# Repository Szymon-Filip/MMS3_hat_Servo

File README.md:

# Hat 4-kanałowy sterownik serw

## Sekcja 1: Dokumentacja Hat'a

### Krótki opis projektu
Hat to 4-kanałowy sterownik serw, bazujący na  generatorze PWM **PCA9685PW** (komunikacja I2C). Zasialnie serw jest z XT60

### Zgodność ze standardem ChainBus

* ✅ Używa złącza ChainBus, nie zmienia jego miejsca ani pinoutu.
* ✅ Używa wyłącznie interfejsów I2C, SPI lub UART i nie inicjuje samodzielnie nowych transmisji (Nie jest master'em I2C albo SPI).
* ✅ Spełnia wymagania mechaniczne standardu (wymiary PCB, rozstaw otworów).
* ✅ Pobiera maksymalny prąd zgodny z ilością na jednego hat'a
* ✅ Obsługuje napięcie wejściowe BRD_VIN do wartości 48V.

### Komunikacja i adresowanie

#### Adresacja I2C
Komunikacja z PCA9685PW odbywa się za pomocą magistrali I2C. Wszystkie linie adresowe układu PCA9685PW (A0, A1, A2, A3, A4, A5) są podłączone do napięcia 5V.

| Układ (IC)    | Funkcja                          | Adres I2C (7-bit) |
| :------------ | :------------------------------- | :---------------: |
| **PCA9685PW** | 16-kanałowy generator PWM 12-bit | `1111111b` (0x7F) |

---

### Przypisanie kanałów generatora PCA9685

Układ PCA9685 steruje bezpośrednio czterema wyjściami serw oraz dwoma debug diodami LED:

| Wyjście PCA9685 | Powiązany element | Typ złącza  | Opis                              |
| :-------------: | :---------------- | :---------- | :-------------------------------- |
|    **LED0**     | Servo 1           | **J10**     | Kanał sterujący serwomechanizmu 1 |
|    **LED1**     | Servo 2           | **J9**      | Kanał sterujący serwomechanizmu 2 |
|    **LED2**     | Servo 3           | **J8**      | Kanał sterujący serwomechanizmu 3 |
|    **LED3**     | Servo 4           | **J7**      | Kanał sterujący serwomechanizmu 4 |
|    **LED14**    | Debug LED         | *Na płycie* | Dioda LED do debugowania          |
|    **LED15**    | Debug LED         | *Na płycie* | Dioda LED do debugowania          |

---

### Pinout złączy serwomechanizmów (J7 – J10)

Każde złącze wyjściowe (J7, J8, J9, J10) posiada 3 piny w następującym układzie:

| Pin   | Nazwa sygnału | Poziom napięcia    | Opis                                       |
| :---- | :------------ | :----------------- | :----------------------------------------- |
| **1** | `GND`         | 0 V                | Wspólna masa układu                        |
| **2** | `SERVO` (PWM) | 5 V                | Sygnał sterujący PWM z układu PCA9685      |
| **3** | `VCC`         | `BRD_VIN` (z XT60) | Napięcie zasilające silnik serwomechanizmu |

> **⚠️ UWAGA DOTYCZĄCA BEZPIECZEŃSTWA (PINOUT):**
> Układ wyprowadzeń złączy na tym module to **[1: GND, 2: Sygnał, 3: VCC]**. Jest on odmienny od klasycznego modelarskiego standardu wtyczek serwomechanizmów (gdzie pin zasilania VCC zazwyczaj znajduje się w środku wtyku).
>
> Przed podłączeniem serwomechanizmu należy bezwzględnie zweryfikować kolejność przewodów w wiązce serwa. Błędne podłączenie może skutkować uszkodzeniem serwa lub obwodów zasilania modułu.

---

### Szczegółowy opis techniczny

#### Zasilanie serwomechanizmów (`VCC`)
Prąd zasilania serwomechanizmów nie obciąża wewnętrznych linii zasilających magistrali ChainBus. Napięcie doprowadzane jest bezpośrednio ze złącza wysokoprądowego **XT60** na pin 3 każdego złącza serwa. Zasilanie z XT-60 od razu idzie na szyne VIN ChainBus'a. Jeśli potrzebujesz zasilić serwa innym napięciem niż takim samym jak VIN ChainBus'a to odlutuj D1 (tą diode po lewej stronie do której idzie taka duża ścieżka)

#### Sterowanie sygnałem PWM
PWM jest na 5V, ale szyna I2C na 3V3 więc wszystko śmiga jak powinno

---

### Gotowe arkusze hierarchiczne
W projekcie wydzielono i zastosowano następujące arkusze hierarchiczne:
* **Servo_controller** – Schemat generatora PWM PCA9685 z konwerterem I2C 3v3 <-> 5V i zworkami do wybierania adresu I2C

---

## Sekcja 2: Specyfikacja standardu ChainBus

### Architektura i łączenie modułów
Standard ChainBus umożliwia modułowe łączenie hatów. Na jednym MMS3 można zamontować pionowo **do 8 hat'ów**. Połączenie realizowane jest poprzez wpięcie złącza męskiego kolejnego hat'a w złącze żeńskie poprzedniego.

### Komunikacja i sterowanie
Magistrala ChainBus jest w pełni cyfrowa. Płyta główna nie steruje bezpośrednio sygnałami ogólnego przeznaczenia (GPIO) na poszczególnych hat'ach. Wszelkie operacje (np. generowanie sygnałów PWM, obsługa diod) muszą być realizowane przez dedykowane układy scalone komunikujące się przez interfejsy systemowe.

Wybór aktywnego modułu realizowany jest przez układ przełącznika magistrali (bus switch) na płycie głównej. Dzięki temu linie I2C, SPI i UART są niezależne dla każdego hat'a (brak konfliktów adresów I2C między różnymi hatami).
* **Identyfikacja:** Każdy moduł powinien posiadać pamięć EEPROM na magistrali I2C w celu identyfikacji płyty przez system - układ M24C64-W skonfigurowany na adres `1010000` przy liniach adresowych A0, A1, A2 zwartych do masy.

### Zasilanie
Złącze ChainBus dostarcza następujące linie zasilania:

| Magistrala zasilania | Napięcie znamionowe | Maksymalny prąd (łączny dla 8 hatów) | Szacowany prąd na jeden hat |
| :------------------- | :-----------------: | :----------------------------------: | :-------------------------: |
| **5V**               |        5.0 V        |                1.0 A                 |           125 mA            |
| **12V stby**         |       12.0 V        |                0.5 A                 |            65 mA            |
| **BRD_VIN**          |   12.0 V – 48.0 V   |                1.5 A                 |           185 mA            |

*   W przypadku zapotrzebowania na wyższą moc (jak w przypadku tego modułu sterowania serwami), stosuje się dodatkowe złącze zasilania XT60 (obciążalność do ok. 60 A).

---

## Sekcja 3: Licencja, linki i tagi

### Licencjonowanie projektu

*   **PCB:** [CERN-OHL-W](https://ohwr.org/project/cernohl/wikis/Documents/CERN-OHL-version-2) - Umożliwia modyfikacje i sprzedaż pod warunkiem zachowania informacji o oryginalnym autorze. Zmiany muszą być open source.
*   **Software:** [MIT License](https://opensource.org/licenses/MIT) - Umożliwia modyfikacje i sprzedaż komercyjną pod warunkiem zachowania informacji o autorze (zmiany nie muszą być udostępniane jako open source).

### Tagi projektu
#chainbus #MMS3 #ModuCard

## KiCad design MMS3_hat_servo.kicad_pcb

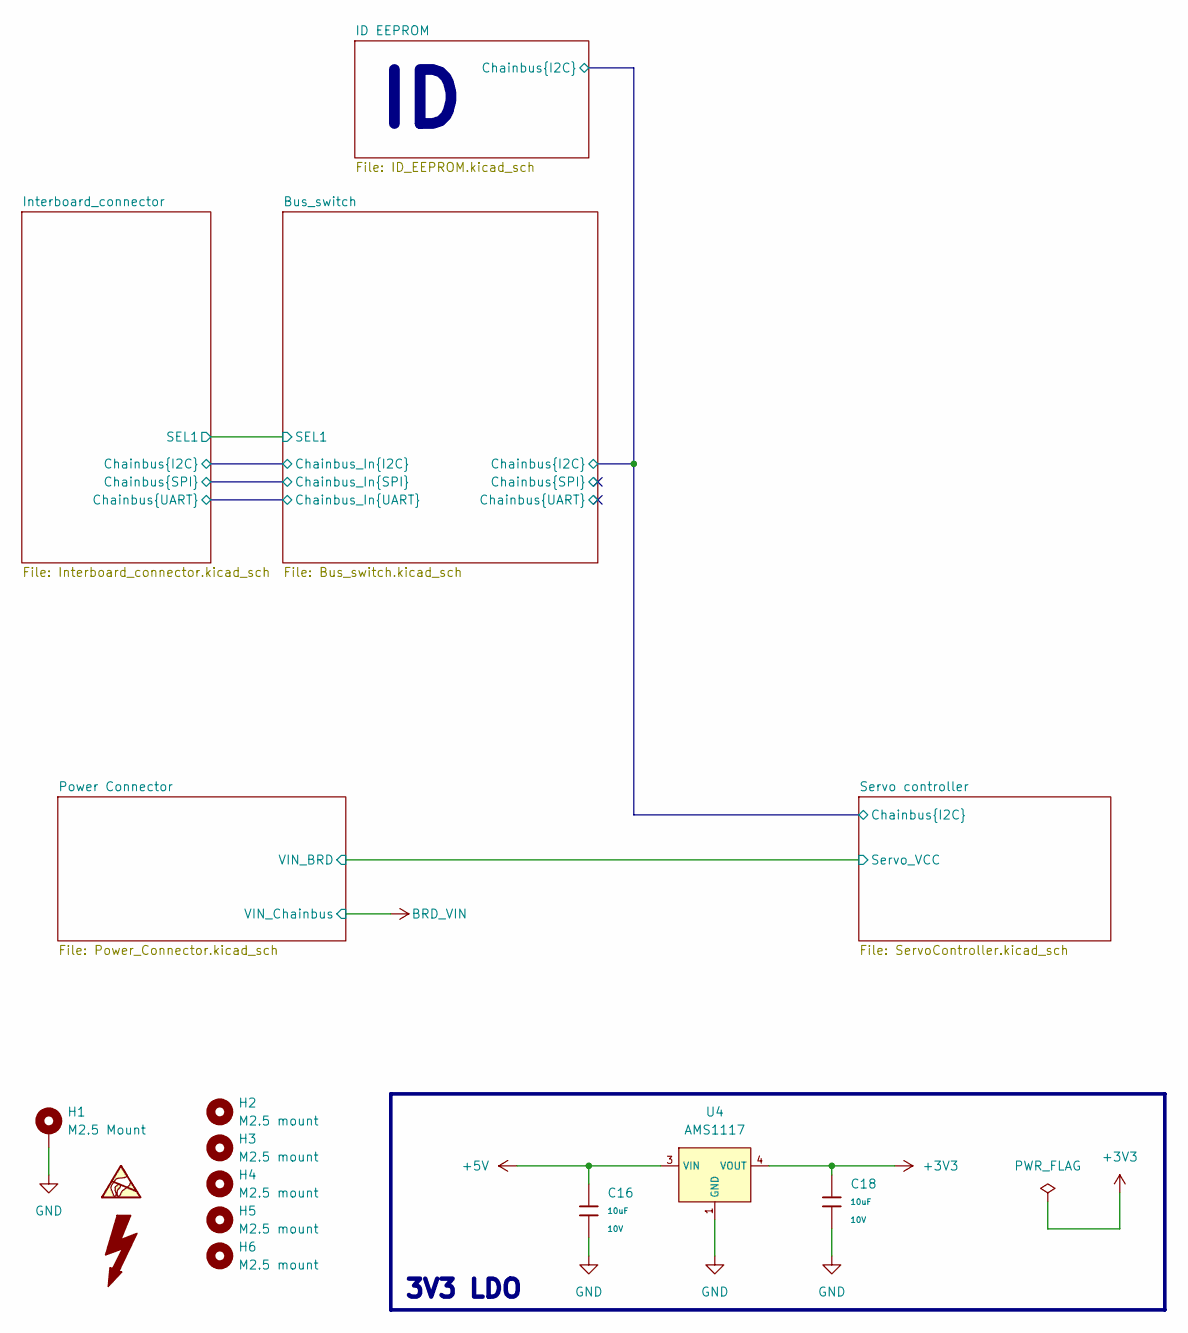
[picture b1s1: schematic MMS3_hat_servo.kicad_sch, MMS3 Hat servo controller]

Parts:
C16, C18: 10uF; C_0603; Voltage Rated 10V; Tolerance ±10%; Part CL10A106KP8NNNC; LCSC C19702
H1: M2.5 Mount; MountingHole_2.7mm_M2.5_DIN965_Pad_TopOnly
H2, H3, H4, H5, H6: M2.5 mount; MountingHole_2.7mm_M2.5
U4: AMS1117; SOT-223-3_L6.5-W3.4-P2.30-LS7.0-BR; Output Voltage 3.3V; Dropout Voltage 1.3V@(800mA); Part AMS1117-3.3; LCSC C6186

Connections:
+3V3: C18.1, U4.2 (VOUT), U4.4 (VOUT); also elsewhere on the board
+5V: C16.1, U4.3 (VIN); also elsewhere on the board
GND: C16.2, C18.2, H1.1 (1_1), U4.1 (GND); also elsewhere on the board

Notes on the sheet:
3V3 LDO

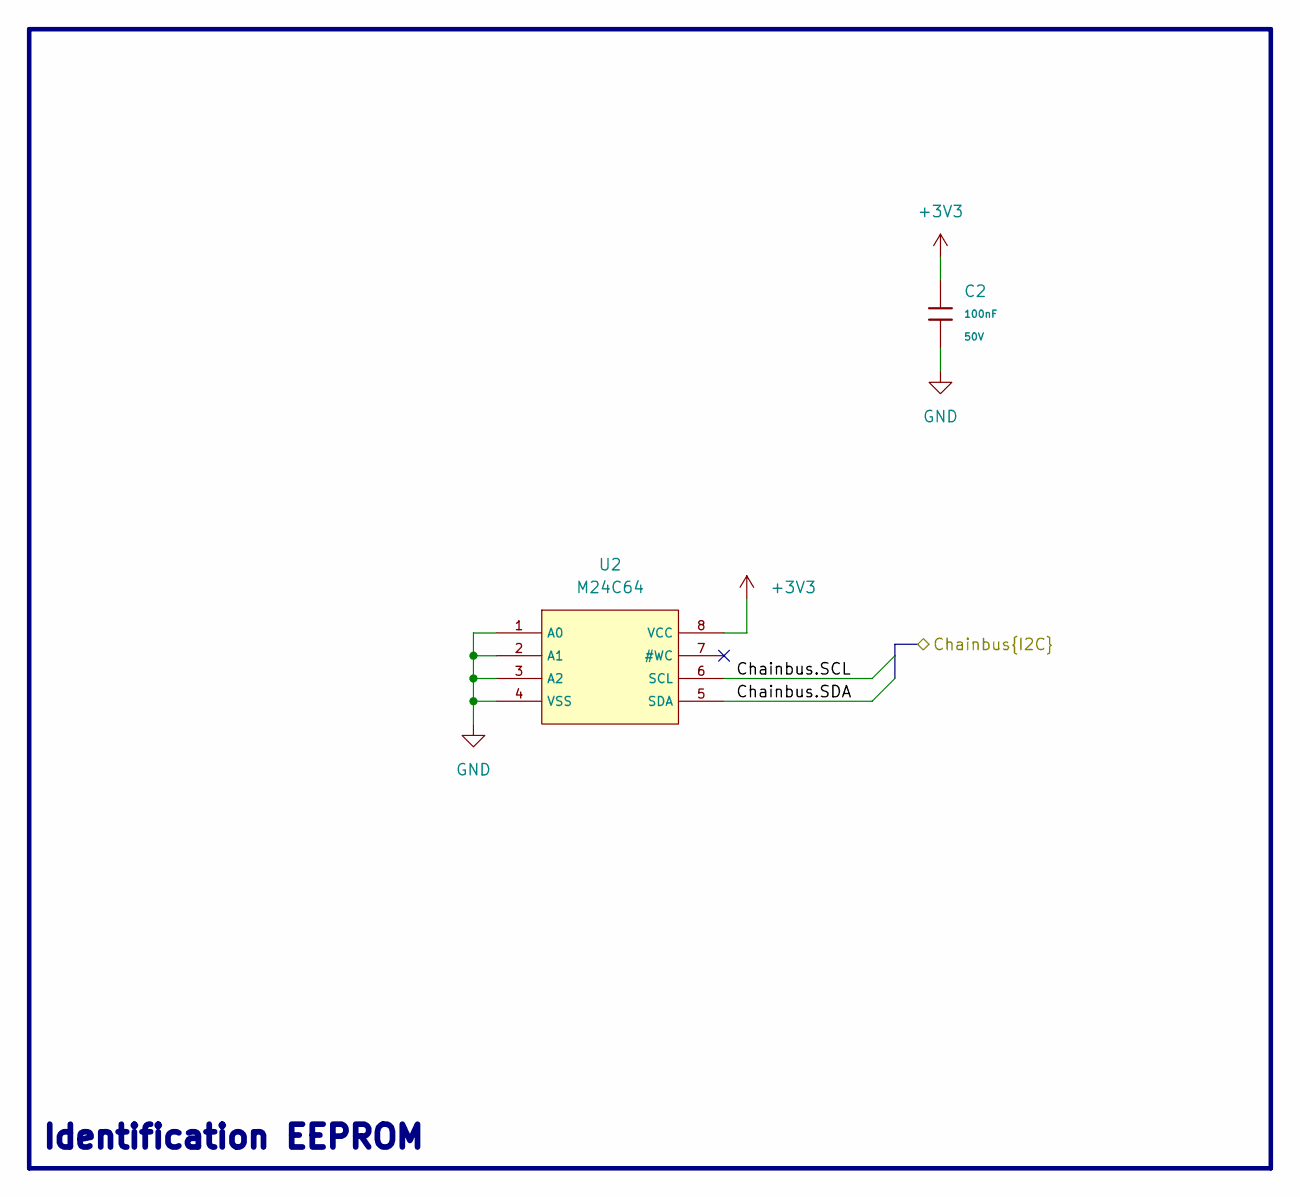
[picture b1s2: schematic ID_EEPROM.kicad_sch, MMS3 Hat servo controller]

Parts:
C2: 100nF; C_0603; Voltage Rated 50V; Tolerance ±10%; Part CC0603KRX7R9BB104; LCSC C14663
U2: M24C64; SOIC-8_L5.0-W4.0-P1.27-LS6.0-BL; Supply Voltage 1.8V~5.5V; Part M24C64-RMN6TP; LCSC C79988

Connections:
+3V3: C2.1, U2.8 (VCC); also elsewhere on the board
/Bus_switch/Chainbus.SCL: U2.6 (SCL); also elsewhere on the board
/Bus_switch/Chainbus.SDA: U2.5 (SDA); also elsewhere on the board
GND: C2.2, U2.1 (A0), U2.2 (A1), U2.3 (A2), U2.4 (VSS); also elsewhere on the board

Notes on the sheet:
Identification EEPROM

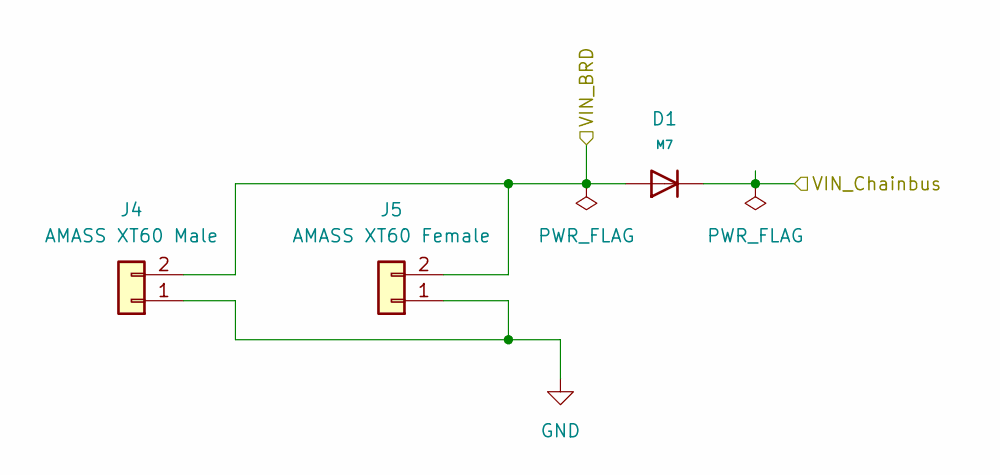
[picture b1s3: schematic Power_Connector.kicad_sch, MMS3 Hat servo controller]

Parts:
D1: M7; D_SMA; Forward Voltage (Vf@If) 1.1V@1A; Reverse Voltage (Vr) 1kV; Part M7; LCSC C95872
J4: AMASS XT60 Male; AMASS_XT60PW-M_1x02_P7.20mm_Horizontal; LCSC C98732
J5: AMASS XT60 Female; AMASS_XT60PW-F_1x02_P7.20mm_Horizontal; LCSC C428722

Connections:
/Power Connector/VIN_BRD: D1.2, J4.2, J5.2; also elsewhere on the board
BRD_VIN: D1.1; also elsewhere on the board
GND: J4.1, J5.1; also elsewhere on the board

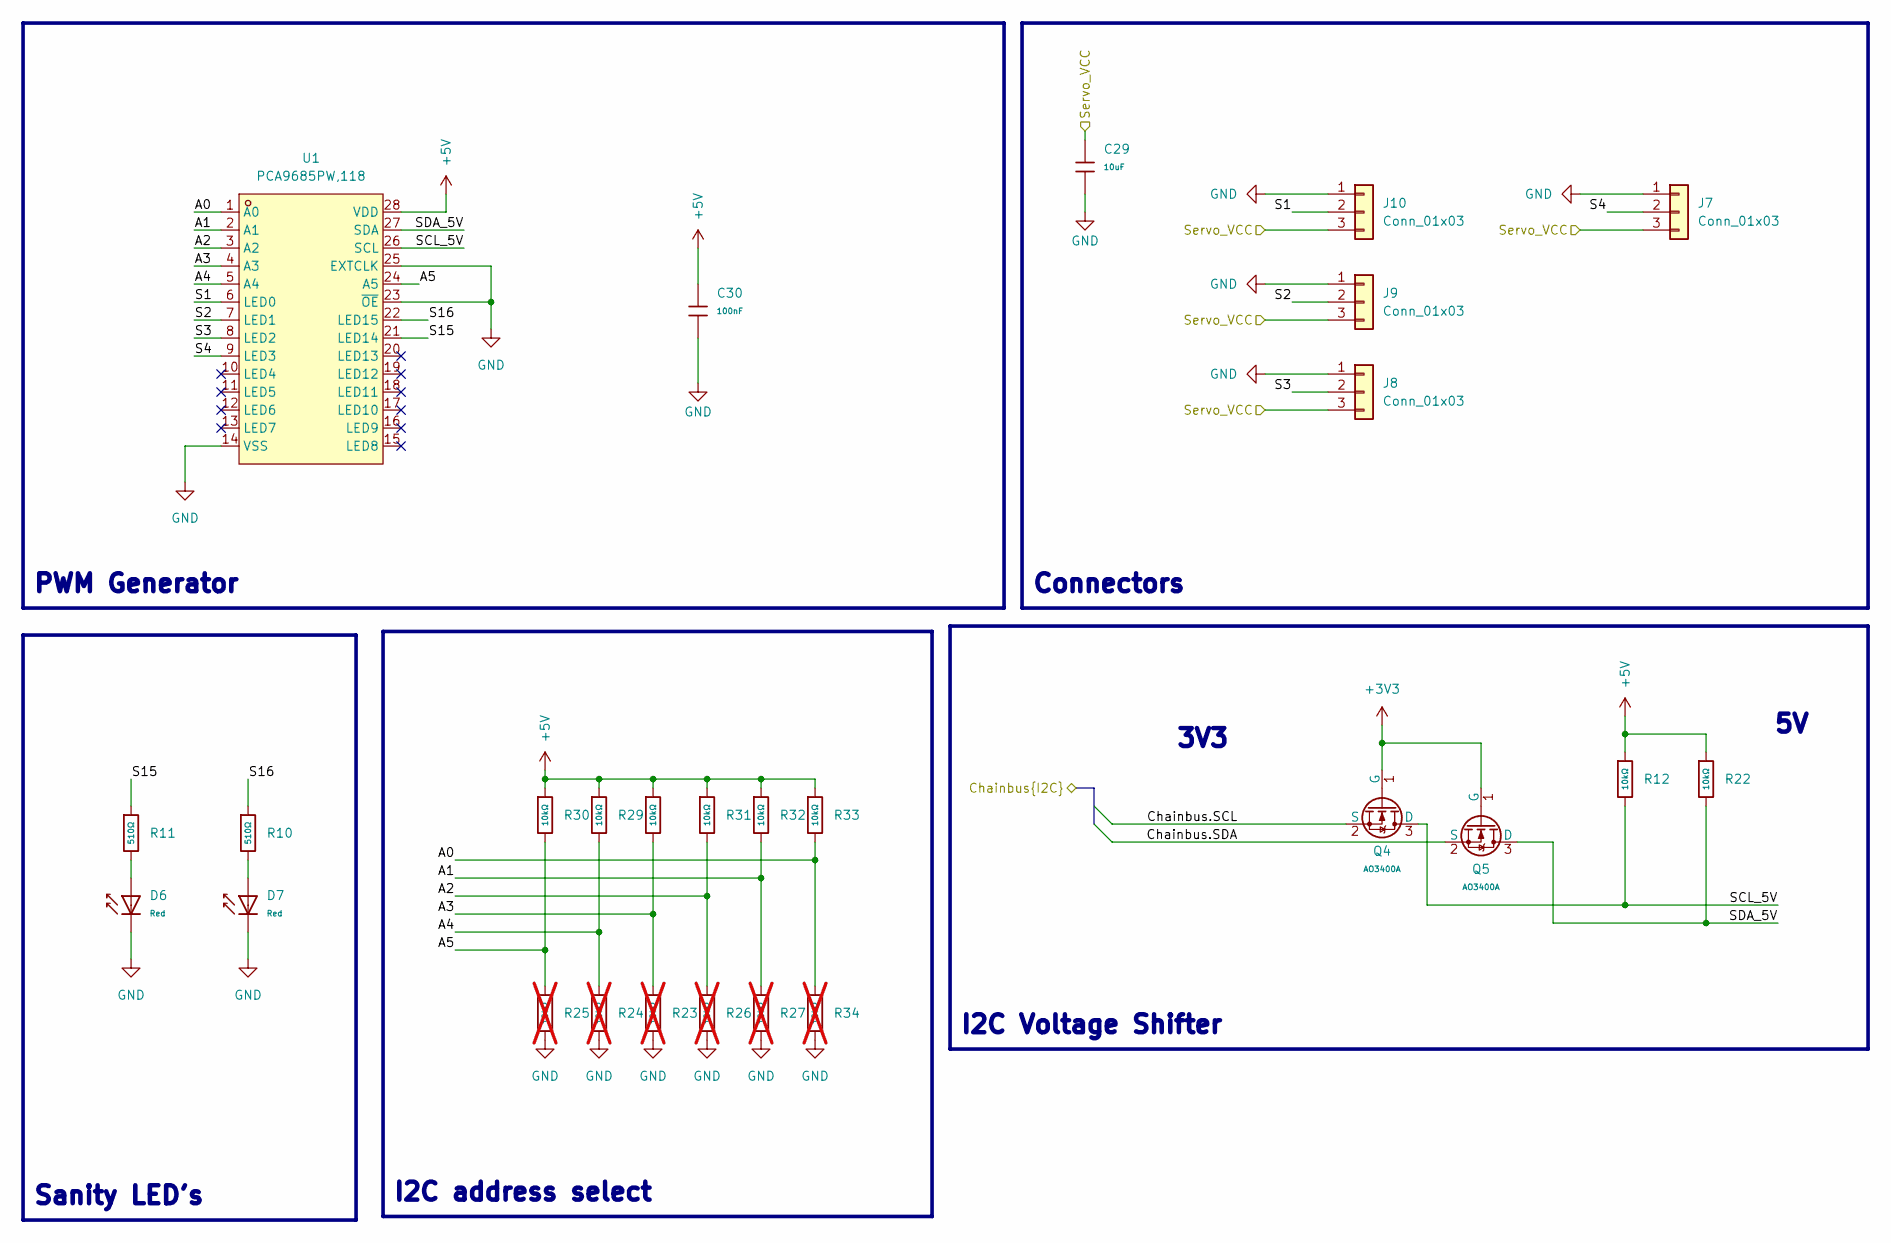
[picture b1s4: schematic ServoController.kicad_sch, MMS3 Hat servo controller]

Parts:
C29: 10uF; C_0603; Voltage Rated 10V; Tolerance ±10%; Part CL10A106KP8NNNC; LCSC C19702
C30: 100nF; C_0603; Voltage Rated 50V; Tolerance ±10%; Part CC0603KRX7R9BB104; LCSC C14663
D6, D7: Red; D_0603; Part KT-0603R; LCSC C2286
J7, J8, J9, J10: Conn_01x03; JST_XH_S3B-XH-A_1x03_P2.50mm_Horizontal
Q4, Q5: AO3400A; Q_SOT-23; Part AO3400A; LCSC C20917
R10, R11: 510Ω; R_0402; Overload Voltage (Max) 50V; Tolerance ±1%; Part 0402WGF5100TCE; LCSC C25123
R12, R22, R28, R29, R30, R31, R32, R33: 10kΩ; R_0402; Overload Voltage (Max) 50V; Tolerance ±1%; Part 0402WGF1002TCE; LCSC C25744
R23, R24, R25, R26, R27, R34: 10kΩ; R_0402; Overload Voltage (Max) 50V; Tolerance ±1%; Part 0402WGF1002TCE; LCSC C25744; not fitted
U1: PCA9685PW,118; TSSOP-28_L9.7-W4.4-P0.65-LS6.4-TL; MPN PCA9685PW,118; LCSC Part C2678753

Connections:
+3V3: Q4.1 (G), Q5.1 (G); also elsewhere on the board
+5V: C30.1, R12.1, R22.1, R28.1, R29.1, R30.1, R31.1, R32.1, R33.1, U1.28 (VDD); also elsewhere on the board
/Bus_switch/Chainbus.SCL: Q4.2 (S); also elsewhere on the board
/Bus_switch/Chainbus.SDA: Q5.2 (S); also elsewhere on the board
/Power Connector/VIN_BRD: C29.1, J7.3, J8.3, J9.3, J10.3; also elsewhere on the board
/Servo controller/A0: R33.2, R34.1, U1.1 (A0)
/Servo controller/A1: R27.1, R32.2, U1.2 (A1)
/Servo controller/A2: R26.1, R31.2, U1.3 (A2)
/Servo controller/A3: R23.1, R28.2, U1.4 (A3)
/Servo controller/A4: R24.1, R29.2, U1.5 (A4)
/Servo controller/A5: R25.1, R30.2, U1.24 (A5)
/Servo controller/S1: J10.2, U1.6 (LED0)
/Servo controller/S2: J9.2, U1.7 (LED1)
/Servo controller/S3: J8.2, U1.8 (LED2)
/Servo controller/S4: J7.2, U1.9 (LED3)
/Servo controller/S15: R11.1, U1.21 (LED14)
/Servo controller/S16: R10.1, U1.22 (LED15)
/Servo controller/SCL_5V: Q4.3 (D), R12.2, U1.26 (SCL)
/Servo controller/SDA_5V: Q5.3 (D), R22.2, U1.27 (SDA)
GND: C29.2, C30.2, D6.1, D7.1, J7.1, J8.1, J9.1, J10.1, R23.2, R24.2, R25.2, R26.2, R27.2, R34.2, U1.14 (VSS), U1.23 (~OE), U1.25 (EXTCLK); also elsewhere on the board
unnamed: D6.2, R11.2
unnamed: D7.2, R10.2

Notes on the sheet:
Sanity LED's
Connectors
I2C Voltage Shifter
PWM Generator
3V3
I2C address select

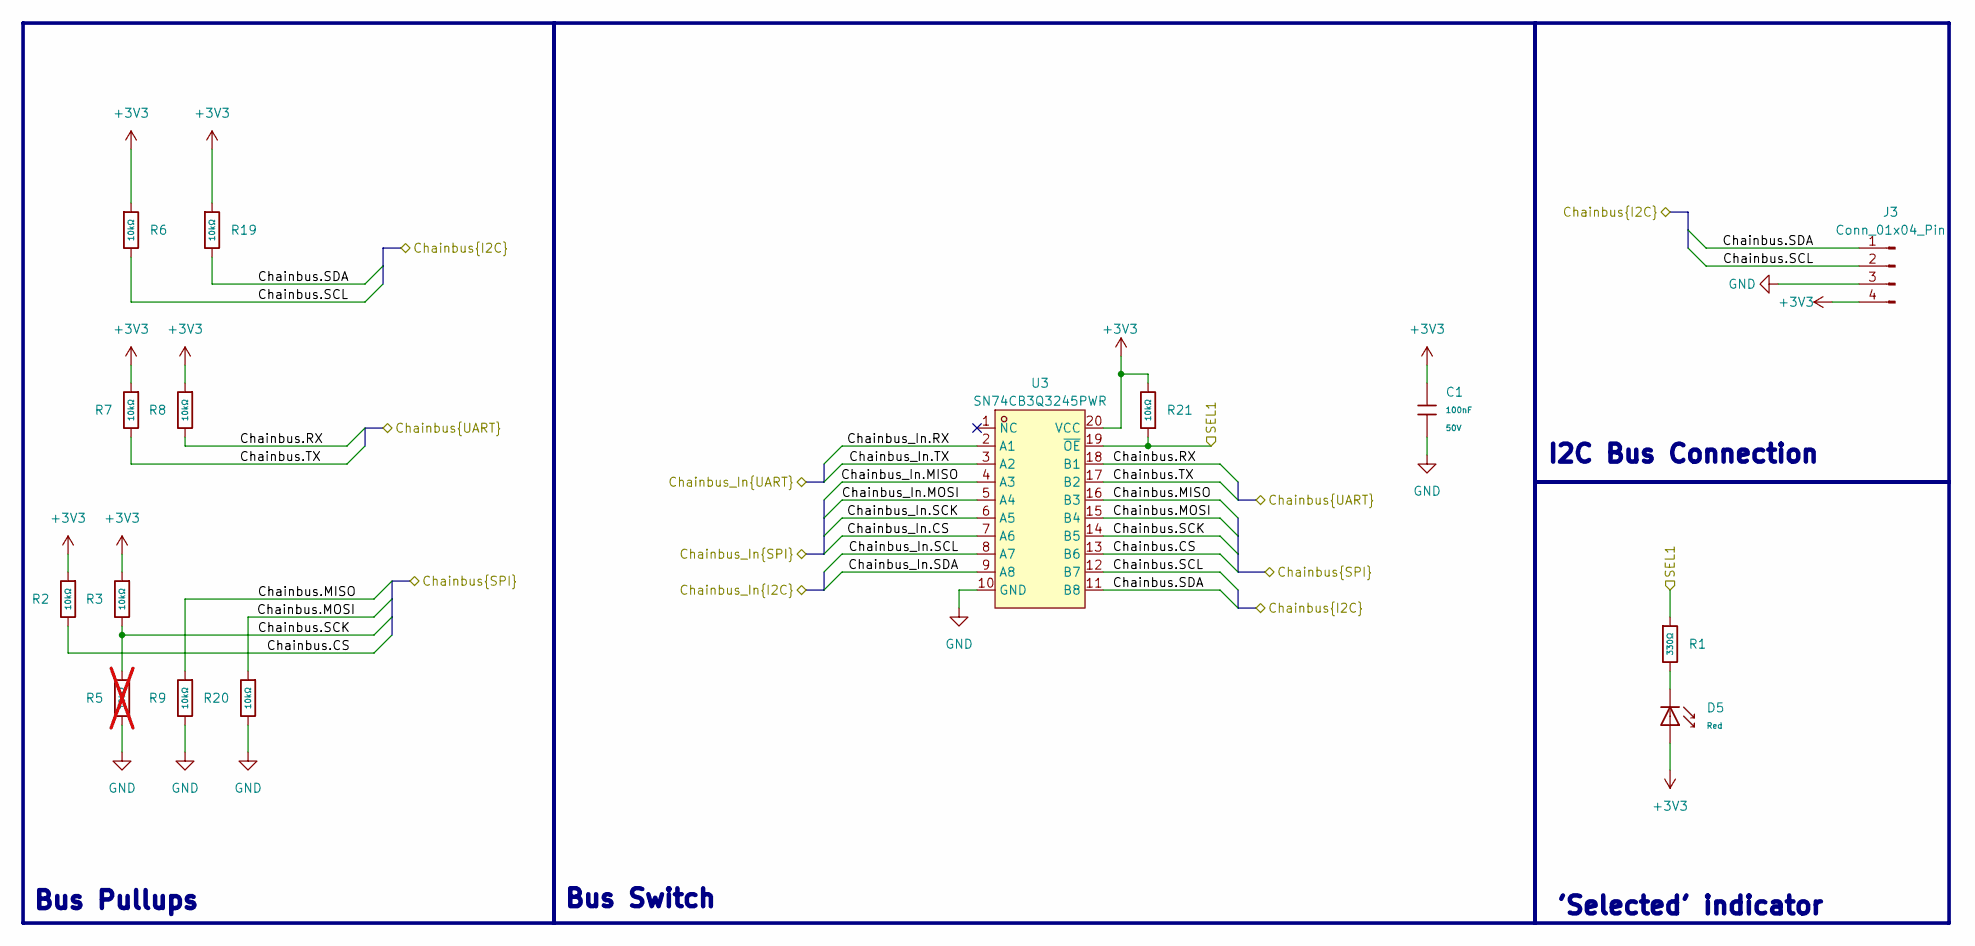
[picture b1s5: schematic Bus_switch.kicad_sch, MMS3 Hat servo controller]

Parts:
C1: 100nF; C_0603; Voltage Rated 50V; Tolerance ±10%; Part CC0603KRX7R9BB104; LCSC C14663
D5: Red; D_0603; Part KT-0603R; LCSC C2286
J3: Conn_01x04_Pin; PinHeader_1x04_P2.54mm_Vertical
R1: 330Ω; R_0402; Overload Voltage (Max) 50V; Tolerance ±1%; Part 0402WGF3300TCE; LCSC C25104
R2, R3, R6, R7, R8, R9, R19, R20, R21: 10kΩ; R_0402; Overload Voltage (Max) 50V; Tolerance ±1%; Part 0402WGF1002TCE; LCSC C25744
R5: 10kΩ; R_0402; Overload Voltage (Max) 50V; Tolerance ±1%; Part 0402WGF1002TCE; LCSC C25744; not fitted
U3: SN74CB3Q3245PWR; TSSOP-20_L6.5-W4.4-P0.65-LS6.4-BL; MPN SN74CB3Q3245PWR; LCSC Part C470961

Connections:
+3V3: C1.1, D5.2, J3.4, R2.1, R3.1, R6.1, R7.1, R8.1, R19.1, R21.2, U3.20 (VCC); also elsewhere on the board
/Bus_switch/Chainbus.CS: R2.2, U3.13 (B6)
/Bus_switch/Chainbus.MISO: R9.1, U3.16 (B3)
/Bus_switch/Chainbus.MOSI: R20.1, U3.15 (B4)
/Bus_switch/Chainbus.RX: R8.2, U3.18 (B1)
/Bus_switch/Chainbus.SCK: R3.2, R5.1, U3.14 (B5)
/Bus_switch/Chainbus.SCL: J3.2, R6.2, U3.12 (B7); also elsewhere on the board
/Bus_switch/Chainbus.SDA: J3.1, R19.2, U3.11 (B8); also elsewhere on the board
/Bus_switch/Chainbus.TX: R7.2, U3.17 (B2)
/Bus_switch/Chainbus_In.CS: U3.7 (A6); also elsewhere on the board
/Bus_switch/Chainbus_In.MISO: U3.4 (A3); also elsewhere on the board
/Bus_switch/Chainbus_In.MOSI: U3.5 (A4); also elsewhere on the board
/Bus_switch/Chainbus_In.RX: U3.2 (A1); also elsewhere on the board
/Bus_switch/Chainbus_In.SCK: U3.6 (A5); also elsewhere on the board
/Bus_switch/Chainbus_In.SCL: U3.8 (A7); also elsewhere on the board
/Bus_switch/Chainbus_In.SDA: U3.9 (A8); also elsewhere on the board
/Bus_switch/Chainbus_In.TX: U3.3 (A2); also elsewhere on the board
/Bus_switch/SEL1: R1.1, R21.1, U3.19 (~OE); also elsewhere on the board
GND: C1.2, J3.3, R5.2, R9.2, R20.2, U3.10 (GND); also elsewhere on the board
unnamed: D5.1, R1.2

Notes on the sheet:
'Selected' indicator
Bus Switch
I2C Bus Connection
Bus Pullups

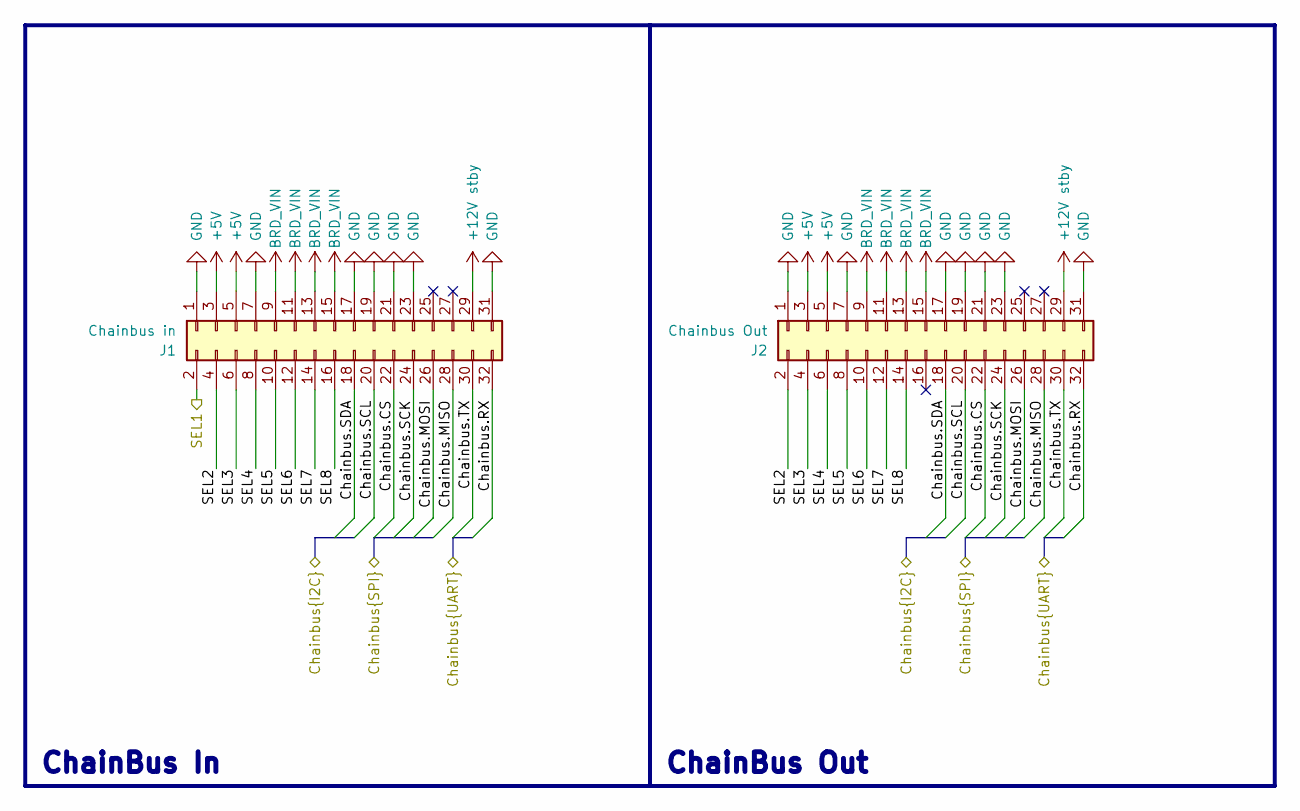
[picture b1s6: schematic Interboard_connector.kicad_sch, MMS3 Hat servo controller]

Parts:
J1: Chainbus in; PinHeader_2x16_P2.54mm_Vertical_SMD
J2: Chainbus Out; PinSocket_2x16_P2.54mm_Vertical_SMD

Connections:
+5V: J1.3, J1.5, J2.3, J2.5; also elsewhere on the board
+12V stby: J1.29, J2.29
/Bus_switch/Chainbus_In.CS: J1.22, J2.22; also elsewhere on the board
/Bus_switch/Chainbus_In.MISO: J1.28, J2.28; also elsewhere on the board
/Bus_switch/Chainbus_In.MOSI: J1.26, J2.26; also elsewhere on the board
/Bus_switch/Chainbus_In.RX: J1.32, J2.32; also elsewhere on the board
/Bus_switch/Chainbus_In.SCK: J1.24, J2.24; also elsewhere on the board
/Bus_switch/Chainbus_In.SCL: J1.20, J2.20; also elsewhere on the board
/Bus_switch/Chainbus_In.SDA: J1.18, J2.18; also elsewhere on the board
/Bus_switch/Chainbus_In.TX: J1.30, J2.30; also elsewhere on the board
/Bus_switch/SEL1: J1.2; also elsewhere on the board
/Interboard_connector/SEL2: J1.4, J2.2
/Interboard_connector/SEL3: J1.6, J2.4
/Interboard_connector/SEL4: J1.8, J2.6
/Interboard_connector/SEL5: J1.10, J2.8
/Interboard_connector/SEL6: J1.12, J2.10
/Interboard_connector/SEL7: J1.14, J2.12
/Interboard_connector/SEL8: J1.16, J2.14
BRD_VIN: J1.9, J1.11, J1.13, J1.15, J2.9, J2.11, J2.13, J2.15; also elsewhere on the board
GND: J1.1, J1.7, J1.17, J1.19, J1.21, J1.23, J1.31, J2.1, J2.7, J2.17, J2.19, J2.21, J2.23, J2.31; also elsewhere on the board

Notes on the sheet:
ChainBus Out
ChainBus In

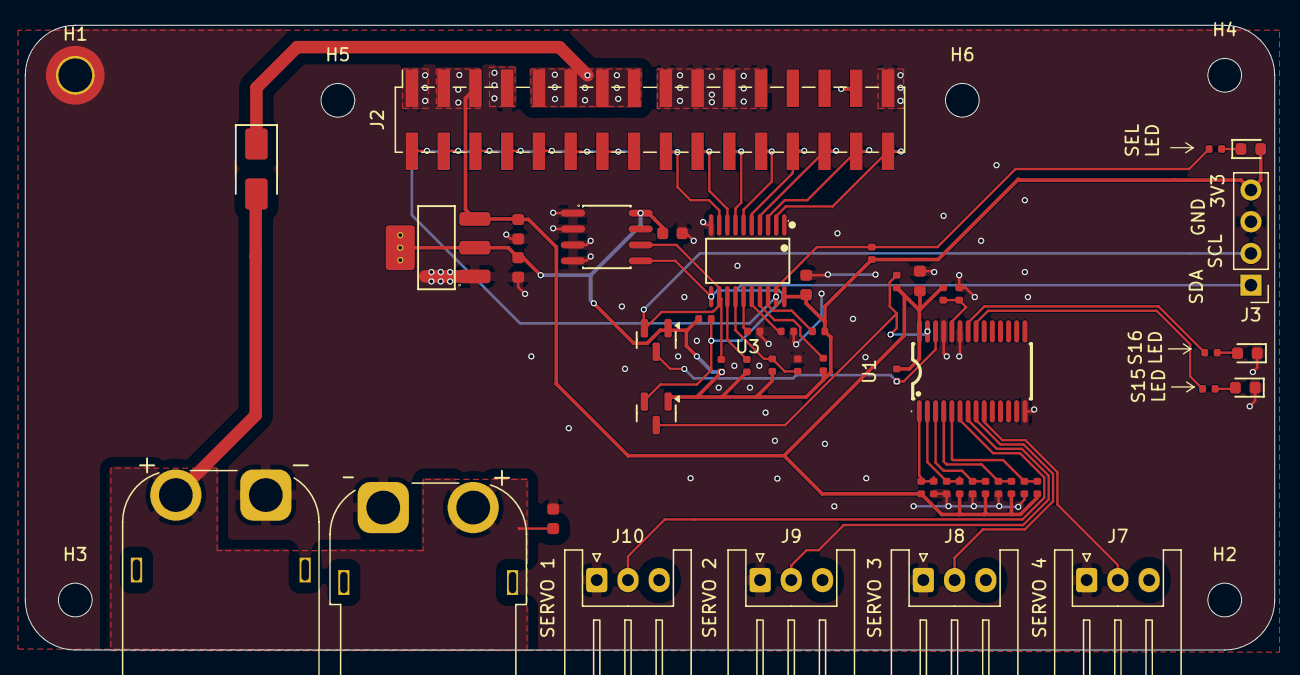
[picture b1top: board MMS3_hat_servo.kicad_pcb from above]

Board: 2 copper layers, 100.0 x 50.0 mm, 58 parts (1 on the bottom side), 47 nets.

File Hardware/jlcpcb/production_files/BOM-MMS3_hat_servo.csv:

Comment,Designator,Footprint,LCSC,Quantity
100nF,"C1,C2,C30",C_0603,C14663,3
10kΩ,"R12,R19,R2,R20,R21,R22,R28,R29,R3,R30,R31,R32,R33,R6,R7,R8,R9",R_0402,C25744,17
10uF,"C16,C18,C29",C_0603,C19702,3
330Ω,R1,R_0402,C25104,1
510Ω,"R10,R11",R_0402,C25123,2
AMS1117,U4,SOT-223-3_L6.5-W3.4-P2.30-LS7.0-BR,C6186,1
AO3400A,"Q4,Q5",Q_SOT-23,C20917,2
M24C64,U2,SOIC-8_L5.0-W4.0-P1.27-LS6.0-BL,C79988,1
M7,D1,D_SMA,C95872,1
"PCA9685PW,118",U1,TSSOP-28_L9.7-W4.4-P0.65-LS6.4-TL,C2678753,1
Red,"D5,D6,D7",D_0603,C2286,3
SN74CB3Q3245PWR,U3,TSSOP-20_L6.5-W4.4-P0.65-LS6.4-BL,C470961,1
Conn_01x03,J10,JST_XH_S3B-XH-A_1x03_P2.50mm_Horizontal,,1
Conn_01x03,J7,JST_XH_S3B-XH-A_1x03_P2.50mm_Horizontal,,1
Chainbus Out,J2,PinSocket_2x16_P2.54mm_Vertical_SMD,,1
Conn_01x03,J9,JST_XH_S3B-XH-A_1x03_P2.50mm_Horizontal,,1
Conn_01x04_Pin,J3,PinHeader_1x04_P2.54mm_Vertical,,1
Conn_01x03,J8,JST_XH_S3B-XH-A_1x03_P2.50mm_Horizontal,,1
Chainbus in,J1,PinHeader_2x16_P2.54mm_Vertical_SMD,,1

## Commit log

2026-04-08 updated Bus switch to one stocked by TME
2026-04-15 Stworzenie wlasnego forka
2026-04-21 ServoController
    Dodano arkusz sterownika servo, aktualizacja polaczen
2026-04-21 Add servo controller details to README
2026-04-21 Update README with additional information on PCA9685PW
    Added note about IC 'ADDR' not being set.
2026-04-21 Poprawa
2026-04-27 polished the schemtic
2026-04-27 updated PCB to up-to-date template:
2026-04-28 added 5V i2c shifter
2026-04-29 PCB design
    In progress
2026-05-03 PCB design
    Adjustments
2026-05-03 Revieved by Wojtek
2026-05-05 change mosfets to basic assembly
2026-06-10 added documentation
2026-06-25 generated gerber
